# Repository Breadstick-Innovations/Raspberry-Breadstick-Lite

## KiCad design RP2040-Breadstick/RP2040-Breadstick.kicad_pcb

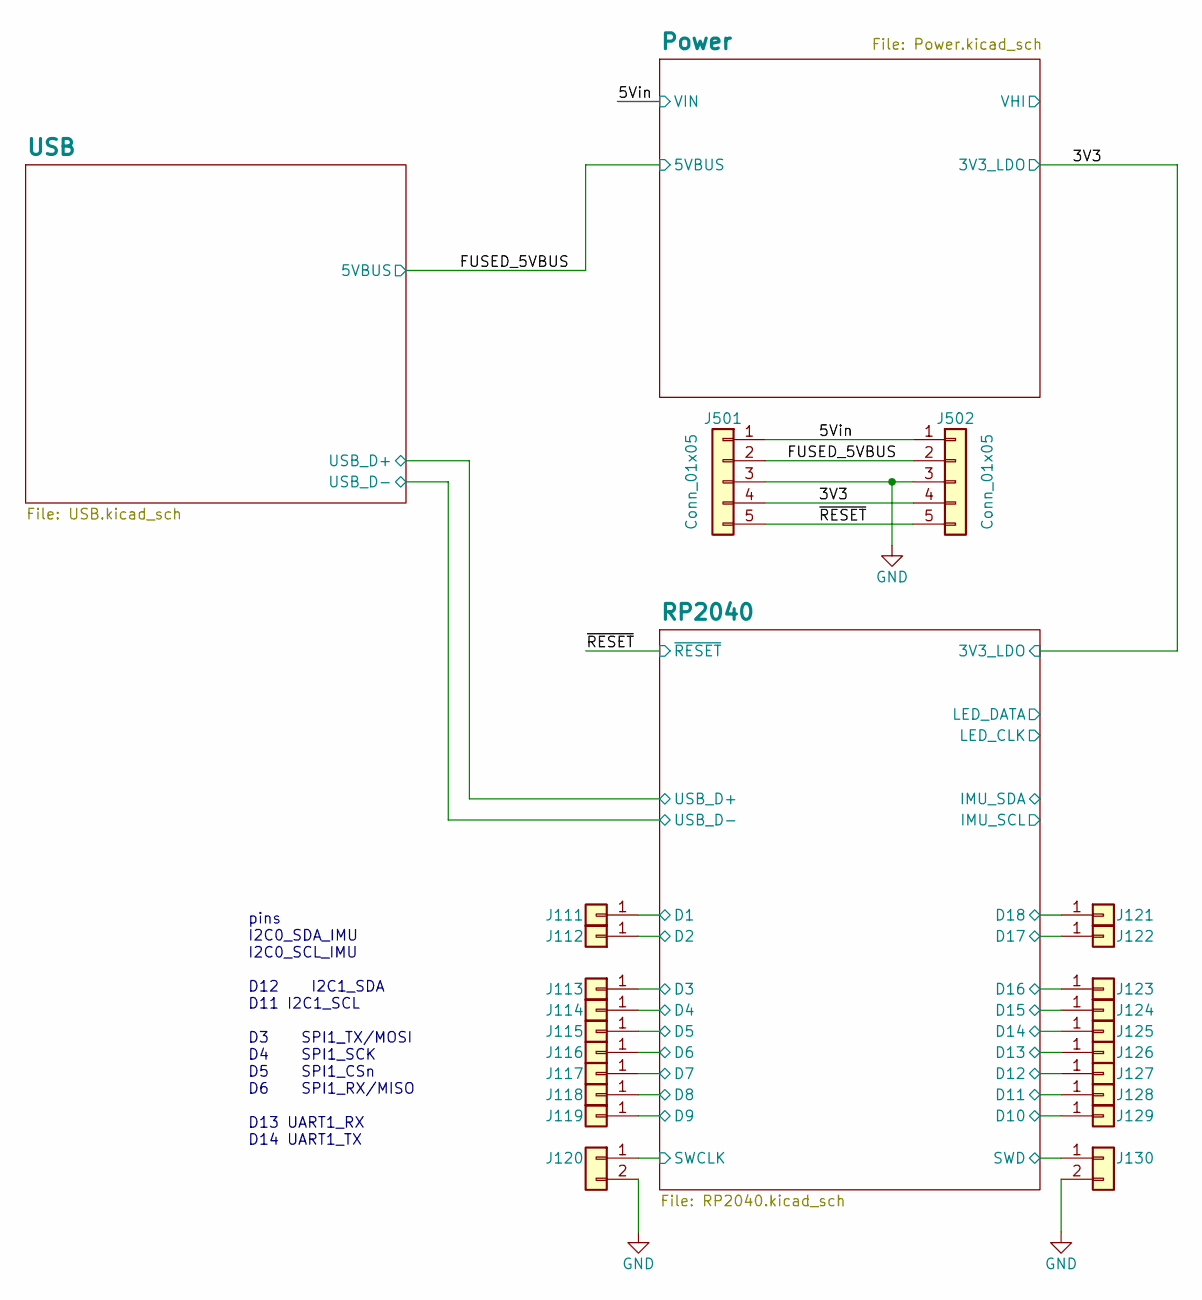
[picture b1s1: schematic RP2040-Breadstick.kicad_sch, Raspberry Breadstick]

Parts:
J111, J112, J113, J114, J115, J116, J117, J118, J119, J121, J122, J123, J124, J125, J126, J127, J128, J129: Conn_01x01; PinHeader_1x01_P2.54mm_Vertical; JLCPCB P/N C492400
J120, J130: Conn_01x02; PinHeader_1x02_P2.54mm_Vertical; JLCPCB P/N C492401
J501, J502: Conn_01x05; PinHeader_1x05_P2.54mm_Vertical; JLCPCB P/N C492404

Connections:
/3V3: J501.4, J502.4; also elsewhere on the board
/5Vin: J501.1, J502.1; also elsewhere on the board
/FUSED_5VBUS: J501.2, J502.2; also elsewhere on the board
/RP2040/D1: J111.1; also elsewhere on the board
/RP2040/D2: J112.1; also elsewhere on the board
/RP2040/D3: J113.1; also elsewhere on the board
/RP2040/D4: J114.1; also elsewhere on the board
/RP2040/D5: J115.1; also elsewhere on the board
/RP2040/D6: J116.1; also elsewhere on the board
/RP2040/D7: J117.1; also elsewhere on the board
/RP2040/D8: J118.1; also elsewhere on the board
/RP2040/D9: J119.1; also elsewhere on the board
/RP2040/D10: J129.1; also elsewhere on the board
/RP2040/D11: J128.1; also elsewhere on the board
/RP2040/D12: J127.1; also elsewhere on the board
/RP2040/D13: J126.1; also elsewhere on the board
/RP2040/D14: J125.1; also elsewhere on the board
/RP2040/D15: J124.1; also elsewhere on the board
/RP2040/D16: J123.1; also elsewhere on the board
/RP2040/D17: J122.1; also elsewhere on the board
/RP2040/D18: J121.1; also elsewhere on the board
/RP2040/SWCLK: J120.1; also elsewhere on the board
/RP2040/SWD: J130.1; also elsewhere on the board
/~RESET: J501.5, J502.5; also elsewhere on the board
GND: J120.2, J130.2, J501.3, J502.3; also elsewhere on the board

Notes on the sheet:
pins I2C0_SDA_IMU I2C0_SCL_IMU D12 I2C1_SDA D11 I2C1_SCL D3 SPI1_TX/MOSI D4 SPI1_SCK D5 SPI1_CSn D6 SPI1_RX/MISO D13 UART1_RX D14 UART1_TX

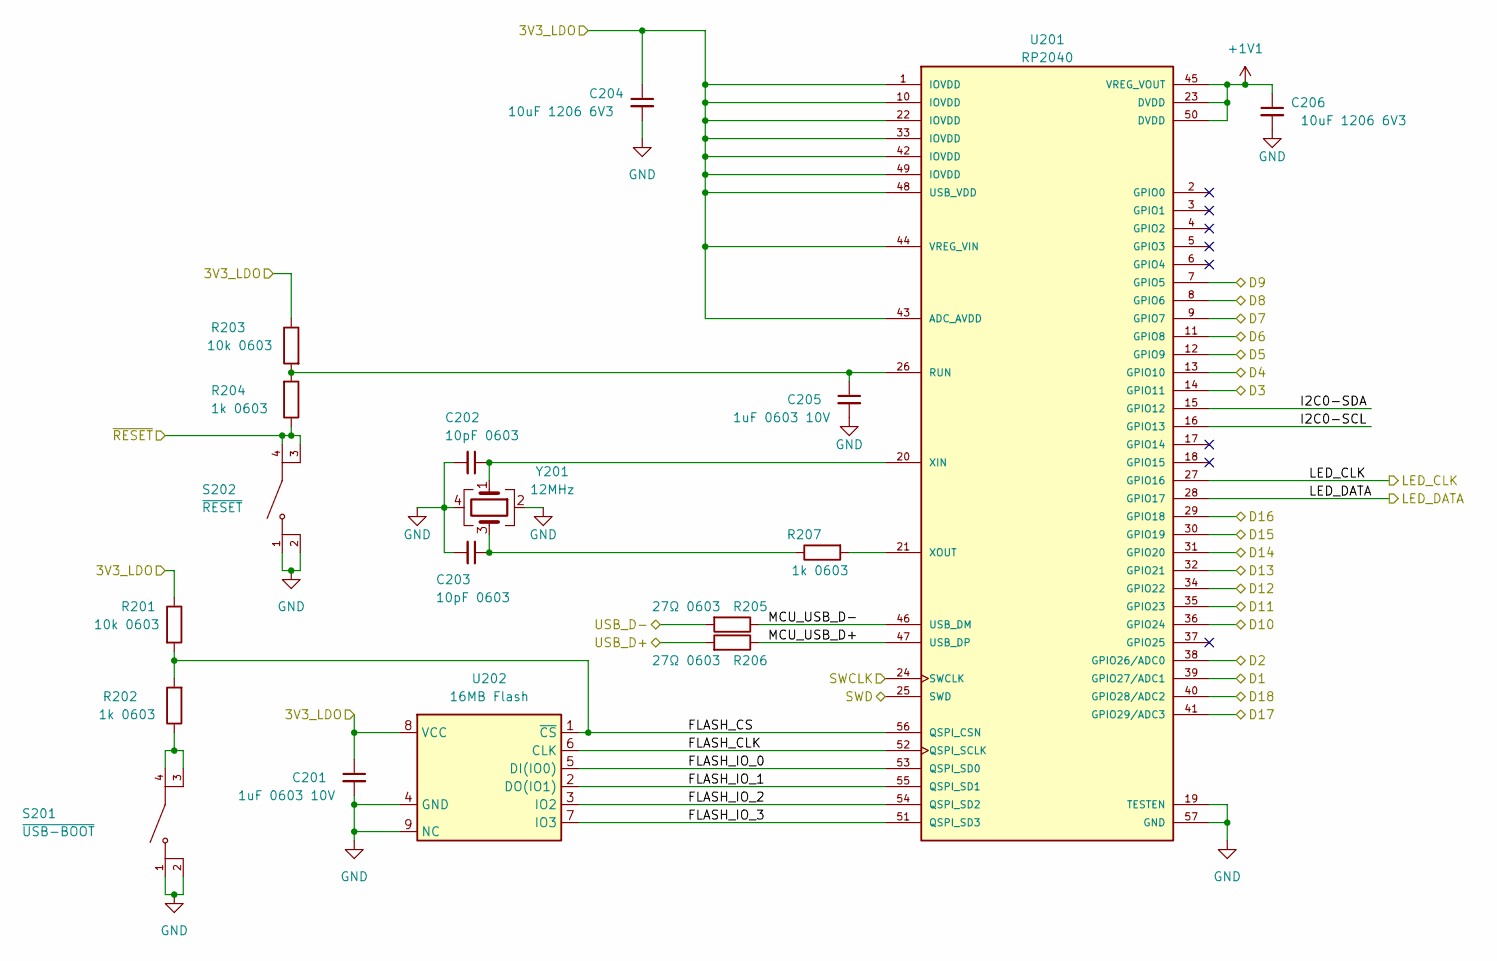
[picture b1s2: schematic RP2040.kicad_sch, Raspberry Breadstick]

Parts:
C201, C205: 1uF 0603 10V; C_0603_1608Metric; Manufacturer_Part_Number CL05A105KP5NNNC; Digikey 1276-1076-6-ND
C202, C203: 10pF 0603; C_0603_1608Metric; Manufacturer_Part_Number 0603N100J500CT; Digikey 1292-1471-1-ND
C204, C206: 10uF 1206 6V3; C_1206_3216Metric; Manufacturer_Part_Number CL31B106KQHNFNE; Digikey 1276-3107-1-ND
R201, R203: 10k 0603; R_0603_1608Metric; Manufacturer_Part_Number RC0603FR-0710KL; Digikey 311-10.0KHRCT-ND
R202, R204, R207: 1k 0603; R_0603_1608Metric; Manufacturer_Part_Number RC0603FR-071KL; Digikey 311-1.00KHRCT-ND
R205, R206: 27Ω 0603; R_0603_1608Metric; Manufacturer_Part_Number RC0603JR-0727RL; Digikey 311-27GRCT-ND
S201: ~{USB-BOOT}; SW_KMR731NGLFS; PARTREV N/A; Digikey CKN10687CT-ND
S202: ~{RESET}; SW_KMR731NGLFS; PARTREV N/A; Digikey CKN10687TR-ND
U201: RP2040; QFN40P700X700X90-57N; PARTREV 1.6.1; JLCPCB P/N C2040
U202: 16MB Flash; W25Q128JVPIQ-TR; Manufacturer_Part_Number W25Q128JVPIQ TR; Digikey W25Q128JVPIQDKR-ND
Y201: 12MHz; XTAL_ECS-120-10-36Q-ES-TR; Manufacturer_Part_Number ECS-120-10-36Q-ES-TR; Digikey XC2180CT-ND

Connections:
+1V1: C206.1, U201.23 (DVDD), U201.45 (VREG_VOUT), U201.50 (DVDD)
/3V3: C201.1, C204.1, R201.1, R203.1, U201.1 (IOVDD), U201.10 (IOVDD), U201.22 (IOVDD), U201.33 (IOVDD), U201.42 (IOVDD), U201.43 (ADC_AVDD), U201.44 (VREG_VIN), U201.48 (USB_VDD), U201.49 (IOVDD), U202.8 (VCC); also elsewhere on the board
/RP2040/D1: U201.39 (GPIO27/ADC1); also elsewhere on the board
/RP2040/D2: U201.38 (GPIO26/ADC0); also elsewhere on the board
/RP2040/D3: U201.14 (GPIO11); also elsewhere on the board
/RP2040/D4: U201.13 (GPIO10); also elsewhere on the board
/RP2040/D5: U201.12 (GPIO9); also elsewhere on the board
/RP2040/D6: U201.11 (GPIO8); also elsewhere on the board
/RP2040/D7: U201.9 (GPIO7); also elsewhere on the board
/RP2040/D8: U201.8 (GPIO6); also elsewhere on the board
/RP2040/D9: U201.7 (GPIO5); also elsewhere on the board
/RP2040/D10: U201.36 (GPIO24); also elsewhere on the board
/RP2040/D11: U201.35 (GPIO23); also elsewhere on the board
/RP2040/D12: U201.34 (GPIO22); also elsewhere on the board
/RP2040/D13: U201.32 (GPIO21); also elsewhere on the board
/RP2040/D14: U201.31 (GPIO20); also elsewhere on the board
/RP2040/D15: U201.30 (GPIO19); also elsewhere on the board
/RP2040/D16: U201.29 (GPIO18); also elsewhere on the board
/RP2040/D17: U201.41 (GPIO29/ADC3); also elsewhere on the board
/RP2040/D18: U201.40 (GPIO28/ADC2); also elsewhere on the board
/RP2040/FLASH_CLK: U201.52 (QSPI_SCLK), U202.6 (CLK)
/RP2040/FLASH_CS: R201.2, R202.2, U201.56 (QSPI_CSN), U202.1 (~CS)
/RP2040/FLASH_IO_0: U201.53 (QSPI_SD0), U202.5 (DI(IO0))
/RP2040/FLASH_IO_1: U201.55 (QSPI_SD1), U202.2 (DO(IO1))
/RP2040/FLASH_IO_2: U201.54 (QSPI_SD2), U202.3 (IO2)
/RP2040/FLASH_IO_3: U201.51 (QSPI_SD3), U202.7 (IO3)
/RP2040/I2C0-SCL: U201.16 (GPIO13)
/RP2040/I2C0-SDA: U201.15 (GPIO12)
/RP2040/LED_CLK: U201.27 (GPIO16)
/RP2040/LED_DATA: U201.28 (GPIO17)
/RP2040/MCU_USB_D+: R206.1, U201.47 (USB_DP)
/RP2040/MCU_USB_D-: R205.1, U201.46 (USB_DM)
/RP2040/SWCLK: U201.24 (SWCLK); also elsewhere on the board
/RP2040/SWD: U201.25 (SWD); also elsewhere on the board
/RP2040/USB_D+: R206.2; also elsewhere on the board
/RP2040/USB_D-: R205.2; also elsewhere on the board
/~RESET: R204.1, S202.3, S202.4; also elsewhere on the board
GND: C201.2, C202.2, C203.2, C204.2, C205.2, C206.2, S201.1, S201.2, S202.1, S202.2, U201.19 (TESTEN), U201.57 (GND), U202.4 (GND), U202.9 (NC), Y201.2, Y201.4; also elsewhere on the board
unnamed: C203.1, R207.1, Y201.3
unnamed: R202.1, S201.3, S201.4
unnamed: C205.1, R203.2, R204.2, U201.26 (RUN)
unnamed: C202.1, U201.20 (XIN), Y201.1
unnamed: R207.2, U201.21 (XOUT)

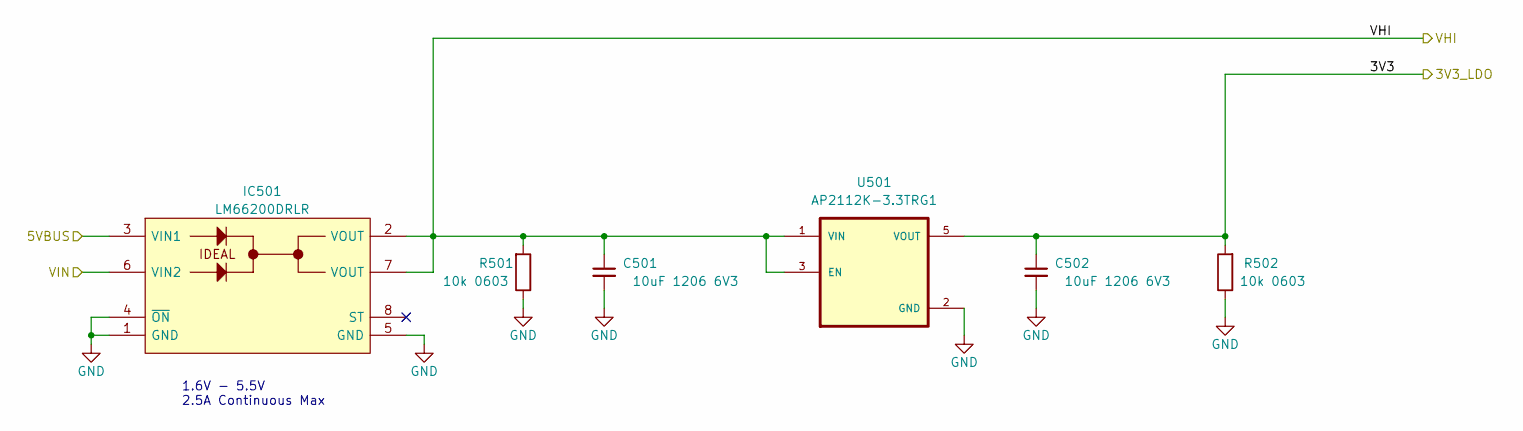
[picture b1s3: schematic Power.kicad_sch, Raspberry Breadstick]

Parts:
C501, C502: 10uF 1206 6V3; C_1206_3216Metric; Manufacturer_Part_Number CL31B106KQHNFNE; Digikey 1276-3107-1-ND
IC501: LM66200DRLR; SOTFL50P160X60-8L; Mouser Part Number 595-LM66200DRLR
R501, R502: 10k 0603; R_0603_1608Metric; Manufacturer_Part_Number RC0603FR-0710KL; Digikey 311-10.0KHRCT-ND
U501: AP2112K-3.3TRG1; SOT95P285X140-5N; PARTREV 2-2; DigiKey_Part_Number AP2112K-3.3TRG1DITR-ND

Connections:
/3V3: C502.1, R502.2, U501.5 (VOUT); also elsewhere on the board
/5Vin: IC501.6 (VIN2); also elsewhere on the board
/FUSED_5VBUS: IC501.3 (VIN1); also elsewhere on the board
/Power/VHI: C501.1, IC501.2 (VOUT), IC501.7 (VOUT), R501.2, U501.1 (VIN), U501.3 (EN)
GND: C501.2, C502.2, IC501.1 (GND), IC501.4 (~ON), IC501.5 (GND), R501.1, R502.1, U501.2 (GND); also elsewhere on the board

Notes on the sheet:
1.6V - 5.5V 2.5A Continuous Max

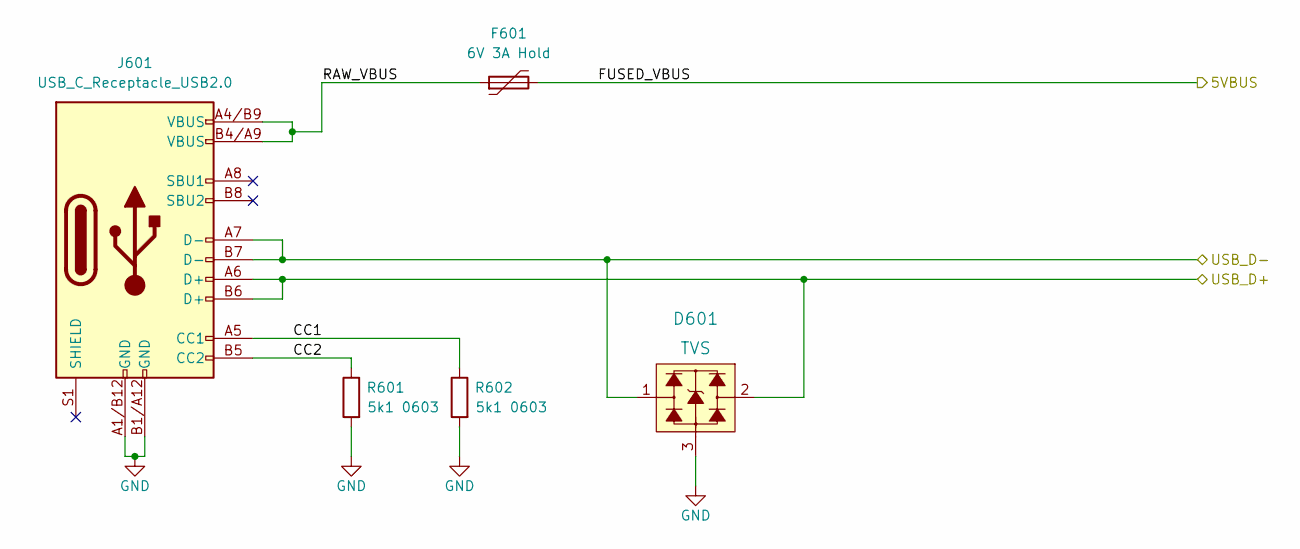
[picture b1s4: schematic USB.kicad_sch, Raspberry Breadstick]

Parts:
D601: TVS; SOT-23; MPN ESDALD05UE2X; Digikey 1740-ESDALD05UE2XCT-ND
F601: 6V 3A Hold; Fuse_1206_3216Metric; Manufacturer_Part_Number PTSLR12066V300; Digikey 283-PTSLR12066V300CT-ND
J601: USB_C_Receptacle_USB2.0; USB-C-2171790001; Manufacturer_Part_Number 2171790001; Digikey 900-2171790001CT-ND
R601, R602: 5k1 0603; R_0603_1608Metric; Manufacturer_Part_Number RC0603FR-075K1L; Digikey 311-5.10KHRCT-ND

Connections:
/FUSED_5VBUS: F601.2; also elsewhere on the board
/RP2040/USB_D+: D601.2, J601.A6 (D+), J601.B6 (D+); also elsewhere on the board
/RP2040/USB_D-: D601.1, J601.A7 (D-), J601.B7 (D-); also elsewhere on the board
/USB/CC1: J601.A5 (CC1), R602.1
/USB/CC2: J601.B5 (CC2), R601.1
/USB/RAW_VBUS: F601.1, J601.A4/B9 (VBUS), J601.B4/A9 (VBUS)
GND: D601.3, J601.A1/B12 (GND), J601.B1/A12 (GND), R601.2, R602.2; also elsewhere on the board

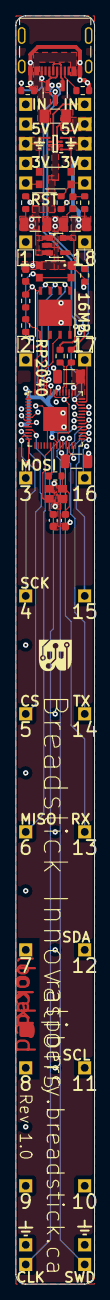
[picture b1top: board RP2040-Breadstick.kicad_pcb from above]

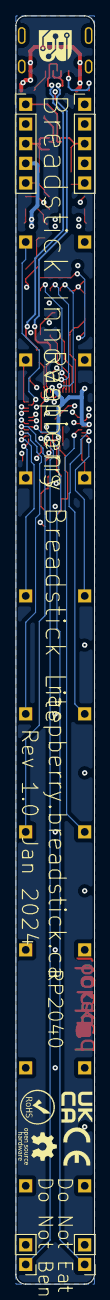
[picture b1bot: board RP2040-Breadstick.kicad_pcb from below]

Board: 6 copper layers, 10.2 x 163.8 mm, 51 parts (22 on the bottom side), 45 nets.

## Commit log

2024-02-13 deleted leds and imu in schematic
2024-02-13 removed parts not needed for LEDs and IMU
2024-02-13 cleaned up unused tracks/vias
2024-02-15 Raspberry Breadstick Lite modifications complete.
2024-02-15 final adjustments before order

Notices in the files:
RP2040-Breadstick/Power.kicad_sch:
Apache-2.0 License
